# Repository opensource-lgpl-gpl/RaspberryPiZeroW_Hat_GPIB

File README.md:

# RaspberryPiZeroW_Hat_GPIB
## A $25.66 Dongle 
### Alternative to GPIB National Instrument's USB-GPIB-HS (MSRP: $1,476) and Prologix GPIB-LAN (MSRP: $189.99): 
This is used to standardize old Lab Instruments (Ammeters and Voltage Sources) like the Kiethley Picoammeter and Voltage Source so that a computer can connect wired via USB-A or wirelessly via bluetooth to a Raspberry Pi Zero with Wifi capabilities. 

This contraption RaspberryPiZeroW_Hat_GPIB can deliver results wirelessly via bluetooth or wired via USB-A (Plug) to USB (Plug) so that results can be delivered wirelessly in order to support work-from-home pandemic initiatives. 

This allows the older lab instruments to have the same capabilities as newer more expensive lab instruments that can cost thousands of dollars. 

This side-project used free and open-source tools to show: 
- Free software like KiCAD can completely replace Altium and intra-convertibility between Altium-to-KiCAD. 
- Free software auto-routing tool FreeRoute can replace most of manual PCB design routing. 
- Free software FreeCAD can completely replace SolidWorks, AutoCAD, et cetera (all costly "CAD" software). 

## Why was this created? 
During my time at NASA, I was tasked with getting a Prologix-LAN (MSRP $189.99) to talk to an old lab instrument: 

I was having a hard time connecting to a Prologix GPIB-Lan that was talking to a Kiethley instrument because when I sent the Prologix controller a command to go into "recieve"/"listen" mode, the logic was inverted; what resulted was the Prologix controller started to spew out a lot of data. Then when I wanted the Prologix controller to give me data or in other words, to "talk," the Prologix controller was silenced and went into "recieve"/"listen" mode. 

So I said to myself: "Why would I want to use a GPIB controller that does the exact opposite of what you want it to? Wouldn't that unpredictability potentially compromise valuable results someday when something invariably goes wrong, and you are trying to look for a root-cause?"

To me, this was not rocket science; I scoured the internet and found Thomas Klima's work on Raspberry Pi Model 3's USB-GPIB. 

Link to thesis paper (I studied German at University of Freie-Universitat, Berlin, Germany in 2013): http://elektronomikon.org//Bakkarbeit%20RasPi-GPIB%20Thomas%20Klima.pdf

I worked on this project about 6-8 hours total; most of the time was spent on tool setup and getting used to KiCAD, FreeCAD, and FreeRoute on a Mac machine.

This $25 dongle RaspberryPiZeroW_Hat_GPIB would be placed on every old lab instrument to modernize/"upgrade" it. 

## Bill of Materials from Digikey and OshPark and Raspberry Pi 
### (Total Cost of Materials)
| Part                               | Unit price  | Quantity | Digikey Part No.    | Price    |
| ---------------------------------- | ----------- | -------- | ------------------- | -------- |
| IC TRANSCEIVER HALF 8/8 20DIP      | 3.69        | 1        | SN75160BN           | $3.69    |
| IC TRANSCEIVER HALF 8/8 20SOIC     | 2.74        | 1        | SN75161BDWR         | $2.74    |
| RES ARRAY 5 RES 3.3K OHM 10SIP     | 0.63        | 2        | 4610X-102-332LF     | $1.26    |
| RES ARRAY 9 RES 6.8K OHM 10SIP     | 0.63        | 2        | 4610X-101-682LF     | $1.26    |
| CAP CER 0805 220NF 100V X7R 5%     | 0.31        | 1        | C0805C224J1REC7800  | $0.31    |
| RES 100 OHM 1% 1/4W 0805           | 0.07        | 20       | RNCP0805FTD100R     | $1.40    |
| Oshpark PCB Fab                    | $5.00       | 1        | N/A                 | $5.00    |
| Raspberry Pi   Zero W              | $10.00      | 1        | N/A                 | $10.00   |
|                                    |             |          | **Total:**          | $25.66   |

## PCB design and schematics. 
### Tool used: KiCAD
#### Cost of Tool used: Free, Open-source
KiCAD is a free alternative to more expensive software suites like Altium. 

## FreeRouting Tool to auto-route the PCB
### Tool used: FreeRouting
#### Cost of Tool used: Free, Open-source
I used the open-source and free tool called FreeRouting (https://freerouting.org) to route the PCB and ensure that a mounting bracket would fit. 

The PCB was designed using Free Routing to prevent cross-talk of wires as well as support a FreeCAD-designed mounting bracket. 

What is shown is the schematics taken from KiCAD. 

## Right Angle Mounting Bracket between the Raspberry Pi Zero W and GPIB Rpi Hat. 
### Tool used: FreeCAD
#### Cost of Tool used: Free, Open-source
This is the mounting bracket that was to be 3D printed using my personal 3D Printer from Monoprice.

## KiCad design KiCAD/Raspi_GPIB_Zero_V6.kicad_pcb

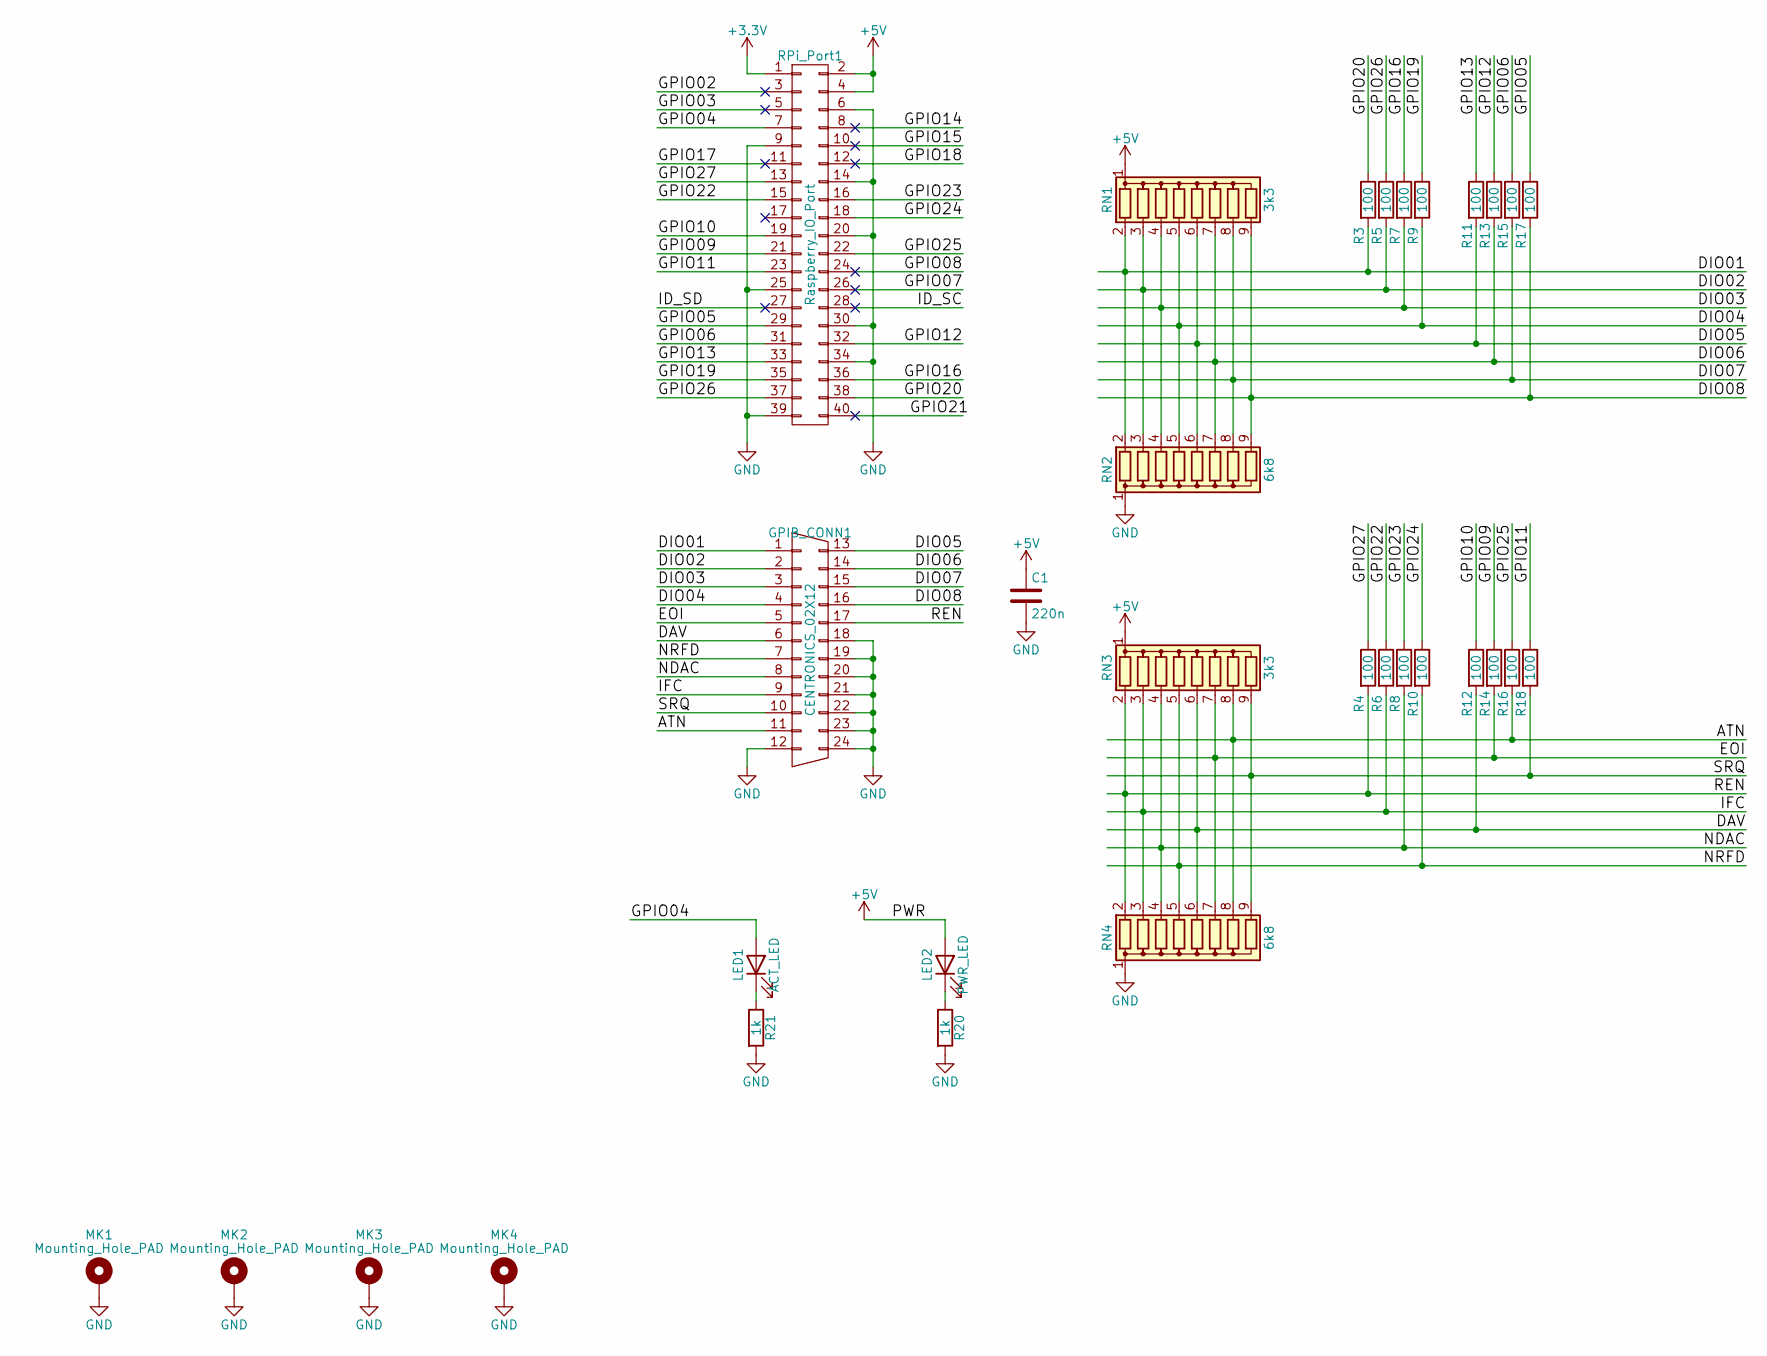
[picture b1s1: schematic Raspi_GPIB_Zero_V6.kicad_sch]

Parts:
C1: 220n; C_0805_2012Metric
GPIB_CONN1: CENTRONICS_02X12; 112024113R001
LED1: ACT_LED; LED_0805_2012Metric
LED2: PWR_LED; LED_0805_2012Metric
MK1, MK2, MK3, MK4: Mounting_Hole_PAD; MountingHole_2.7mm_M2.5_Pad
R3, R4, R5, R6, R7, R8, R9, R10, R11, R12, R13, R14, R15, R16, R17, R18: 100; R_0805_2012Metric
R20, R21: 1k; R_0805_2012Metric
RN1, RN3: 3k3; Resistor_array_SIP9_3k3
RN2, RN4: 6k8; Resistor_array_SIP9_6k8
RPi_Port1: Raspberry_IO_Port; PinHeader_2x20_P2.54mm_Horizontal

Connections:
+3V3: RPi_Port1.1 (3V3)
+5V: C1.1, LED2.2 (A), RN1.1 (common), RN3.1 (common), RPi_Port1.2 (5V), RPi_Port1.4 (5V)
/ATN: GPIB_CONN1.11, R16.2, RN3.8 (R7), RN4.8 (R7)
/DAV: GPIB_CONN1.6, R12.2, RN3.6 (R5), RN4.6 (R5)
/DIO01: GPIB_CONN1.1, R3.2, RN1.2 (R1), RN2.2 (R1)
/DIO02: GPIB_CONN1.2, R5.2, RN1.3 (R2), RN2.3 (R2)
/DIO03: GPIB_CONN1.3, R7.2, RN1.4 (R3), RN2.4 (R3)
/DIO04: GPIB_CONN1.4, R9.2, RN1.5 (R4), RN2.5 (R4)
/DIO05: GPIB_CONN1.13, R11.2, RN1.6 (R5), RN2.6 (R5)
/DIO06: GPIB_CONN1.14, R13.2, RN1.7 (R6), RN2.7 (R6)
/DIO07: GPIB_CONN1.15, R15.2, RN1.8 (R7), RN2.8 (R7)
/DIO08: GPIB_CONN1.16, R17.2, RN1.9 (R8), RN2.9 (R8)
/EOI: GPIB_CONN1.5, R14.2, RN3.7 (R6), RN4.7 (R6)
/GPIO02: RPi_Port1.3 (GPIO2)
/GPIO03: RPi_Port1.5 (GPIO3)
/GPIO04: LED1.2 (A), RPi_Port1.7 (GPIO4)
/GPIO05: R17.1, RPi_Port1.29 (GPIO05)
/GPIO06: R15.1, RPi_Port1.31 (GPIO06)
/GPIO07: RPi_Port1.26 (GPIO07)
/GPIO08: RPi_Port1.24 (GPIO08)
/GPIO09: R14.1, RPi_Port1.21 (GPIO10)
/GPIO10: R12.1, RPi_Port1.19 (GPIO09)
/GPIO11: R18.1, RPi_Port1.23 (GPIO11)
/GPIO12: R13.1, RPi_Port1.32 (GPIO12)
/GPIO13: R11.1, RPi_Port1.33 (GPIO13)
/GPIO14: RPi_Port1.8 (GPIO14)
/GPIO15: RPi_Port1.10 (GPIO15)
/GPIO16: R7.1, RPi_Port1.36 (GPIO16)
/GPIO17: RPi_Port1.11 (GPIO17)
/GPIO18: RPi_Port1.12 (GPIO18)
/GPIO19: R9.1, RPi_Port1.35 (GPIO19)
/GPIO20: R3.1, RPi_Port1.38 (GPIO20)
/GPIO21: RPi_Port1.40 (GPIO21)
/GPIO22: R6.1, RPi_Port1.15 (GPIO22)
/GPIO23: R8.1, RPi_Port1.16 (GPIO23)
/GPIO24: R10.1, RPi_Port1.18 (GPIO24)
/GPIO25: R16.1, RPi_Port1.22 (GPIO25)
/GPIO26: R5.1, RPi_Port1.37 (GPIO26)
/GPIO27: R4.1, RPi_Port1.13 (GPIO27)
/ID_SC: RPi_Port1.28 (ID_SC)
/ID_SD: RPi_Port1.27 (ID_SD)
/IFC: GPIB_CONN1.9, R6.2, RN3.3 (R2), RN4.3 (R2)
/NDAC: GPIB_CONN1.8, R8.2, RN3.4 (R3), RN4.4 (R3)
/NRFD: GPIB_CONN1.7, R10.2, RN3.5 (R4), RN4.5 (R4)
/REN: GPIB_CONN1.17, R4.2, RN3.2 (R1), RN4.2 (R1)
/SRQ: GPIB_CONN1.10, R18.2, RN3.9 (R8), RN4.9 (R8)
GND: C1.2, GPIB_CONN1.12, GPIB_CONN1.18, GPIB_CONN1.19, GPIB_CONN1.20, GPIB_CONN1.21, GPIB_CONN1.22, GPIB_CONN1.23, GPIB_CONN1.24, MK1.1, MK2.1, MK3.1, MK4.1, R20.2, R21.2, RN2.1 (common), RN4.1 (common), RPi_Port1.6 (GND), RPi_Port1.9 (GND), RPi_Port1.14 (GND), RPi_Port1.20 (GND), RPi_Port1.25 (GND), RPi_Port1.30 (GND), RPi_Port1.34 (GND), RPi_Port1.39 (GND)
unnamed: LED1.1 (K), R21.1
unnamed: LED2.1 (K), R20.1

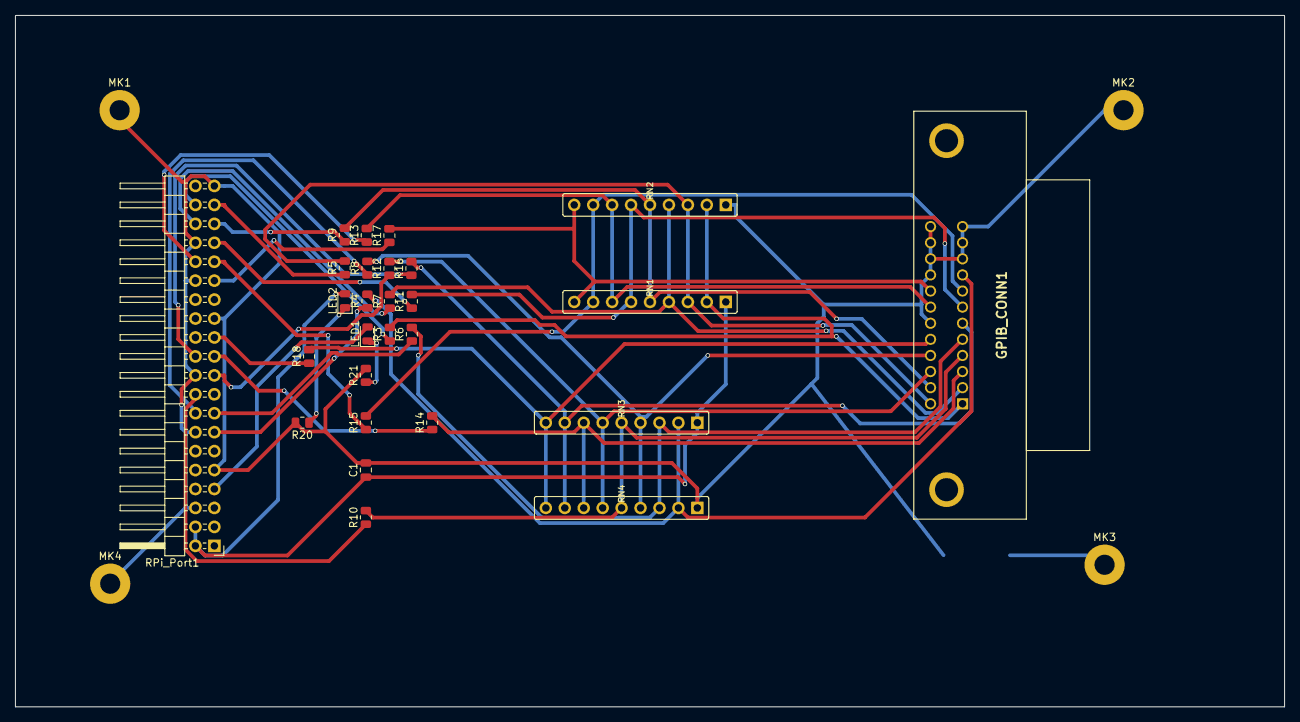
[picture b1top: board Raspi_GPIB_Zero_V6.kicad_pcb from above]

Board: 2 copper layers, 170.2 x 92.7 mm, 31 parts (0 on the bottom side), 37 nets.

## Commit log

2022-03-07 adding to master repository
2022-03-08 Update README.md
    Adding time when I made the GPIB Hat for the raspberry pi.
